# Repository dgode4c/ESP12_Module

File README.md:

View this project on [CADLAB.io](https://cadlab.io/project/23345). 

# ESP12_Module
Schematic and PCB design by shota

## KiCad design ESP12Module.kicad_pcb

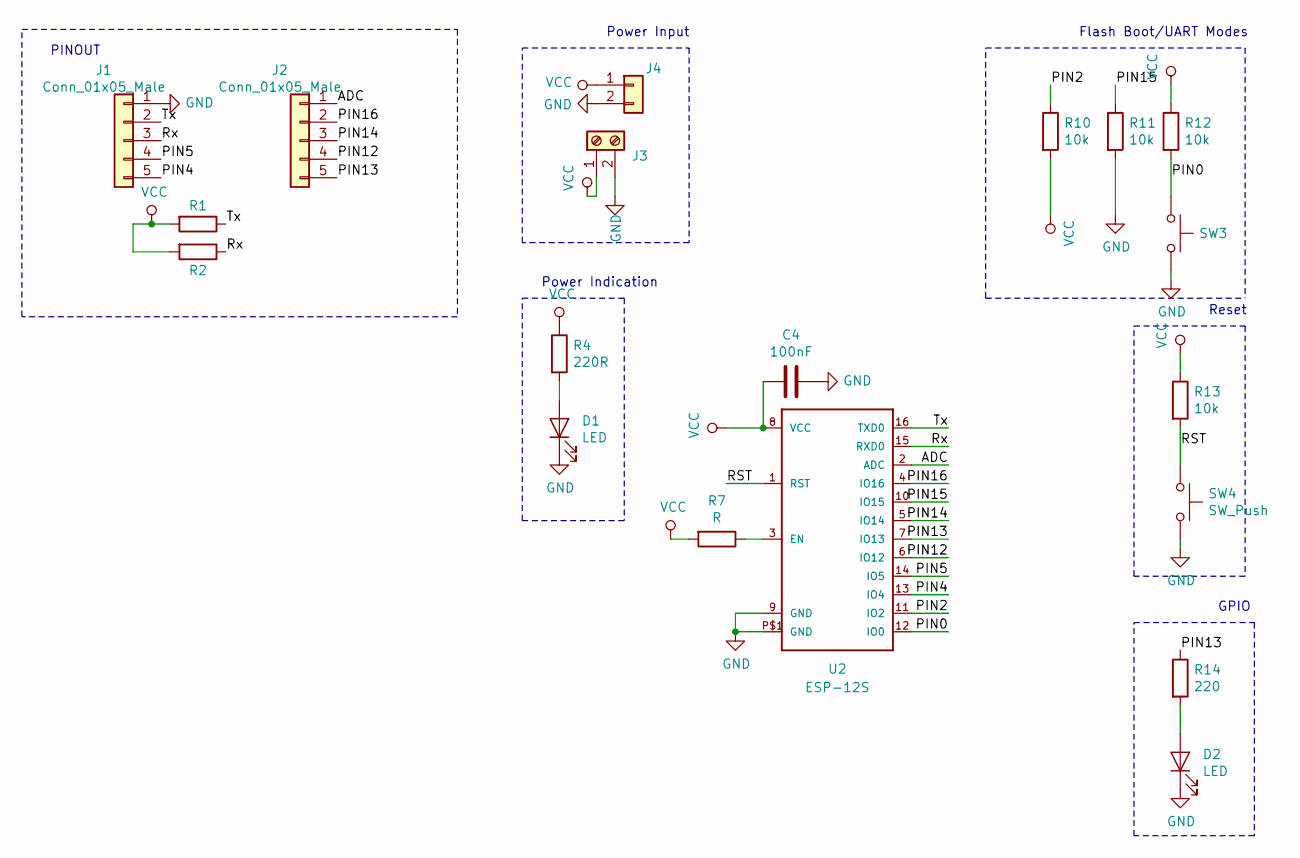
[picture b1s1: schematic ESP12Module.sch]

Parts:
C4: 100nF; C_0805_2012Metric_Pad1.15x1.40mm_HandSolder
D1, D2: LED; LED_0805_2012Metric_Pad1.15x1.40mm_HandSolder
J1, J2: Conn_01x05_Male; PinHeader_1x05_P2.54mm_Vertical
J3: Screw_Terminal_01x02; TerminalBlock01x02
J4: Conn_01x02_Male; PinHeader_1x02_P2.54mm_Vertical
R1, R2, R7: R; R_0805_2012Metric_Pad1.15x1.40mm_HandSolder
R4: 220R; R_0805_2012Metric_Pad1.15x1.40mm_HandSolder
R10, R11, R12, R13: 10k; R_0805_2012Metric_Pad1.15x1.40mm_HandSolder
R14: 220; R_0805_2012Metric_Pad1.15x1.40mm_HandSolder
SW3, SW4: SW_Push; SW_PUSH_6mm
U2: ESP-12S

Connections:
/ADC: J2.1, U2.2 (ADC)
/PIN0: R12.2, SW3.1, U2.12 (IO0)
/PIN2: R10.1, U2.11 (IO2)
/PIN4: J1.5, U2.13 (IO4)
/PIN5: J1.4, U2.14 (IO5)
/PIN12: J2.4, U2.6 (IO12)
/PIN13: J2.5, R14.1, U2.7 (IO13)
/PIN14: J2.3, U2.5 (IO14)
/PIN15: R11.1, U2.10 (IO15)
/PIN16: J2.2, U2.4 (IO16)
/RST: R13.2, SW4.1, U2.1 (RST)
/Rx: J1.3, R2.1, U2.15 (RXD0)
/Tx: J1.2, R1.1, U2.16 (TXD0)
GND: C4.1, D1.1 (K), D2.1 (K), J1.1, J3.2, J4.2, R11.2, SW3.2, SW4.2, U2.9 (GND), U2.P$1 (GND)
unnamed: D1.2 (A), R4.2
unnamed: D2.2 (A), R14.2
unnamed: R7.1, U2.3 (EN)
VCC: C4.2, J3.1, J4.1, R1.2, R2.2, R4.1, R7.2, R10.2, R12.1, R13.1, U2.8 (VCC)

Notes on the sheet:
Reset
Flash Boot/UART Modes
Power Input
Power Indication
GPIO
PINOUT

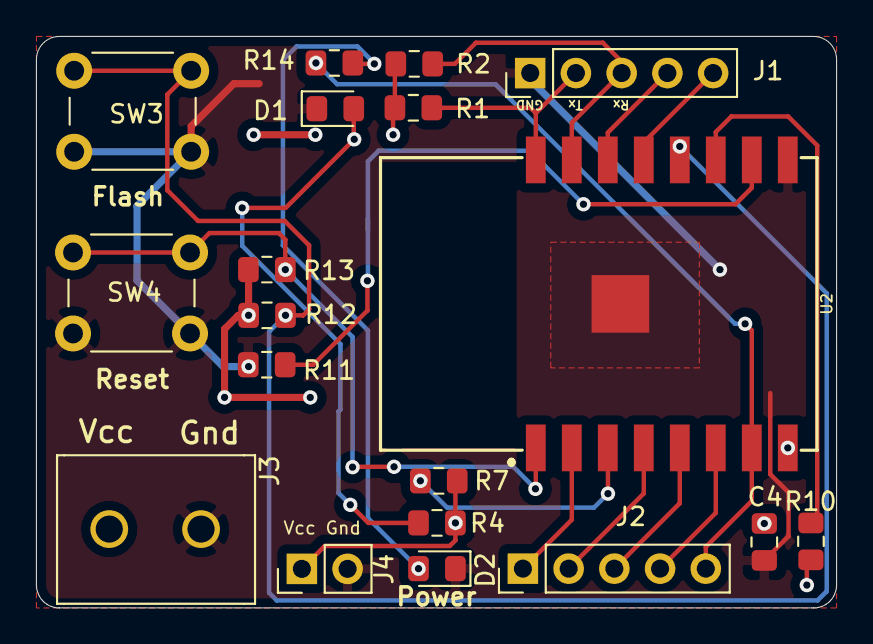
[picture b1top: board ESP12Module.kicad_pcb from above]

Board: 2 copper layers, 44.5 x 31.8 mm, 19 parts (0 on the bottom side), 18 nets.

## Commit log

2020-09-21 Ver. 1.0
2020-09-21 Added amp
2020-09-21 Backlink to CADLAB.io has been added.
2020-09-21 Deleted amp
2020-09-21 Added Vcc Pin On R7
